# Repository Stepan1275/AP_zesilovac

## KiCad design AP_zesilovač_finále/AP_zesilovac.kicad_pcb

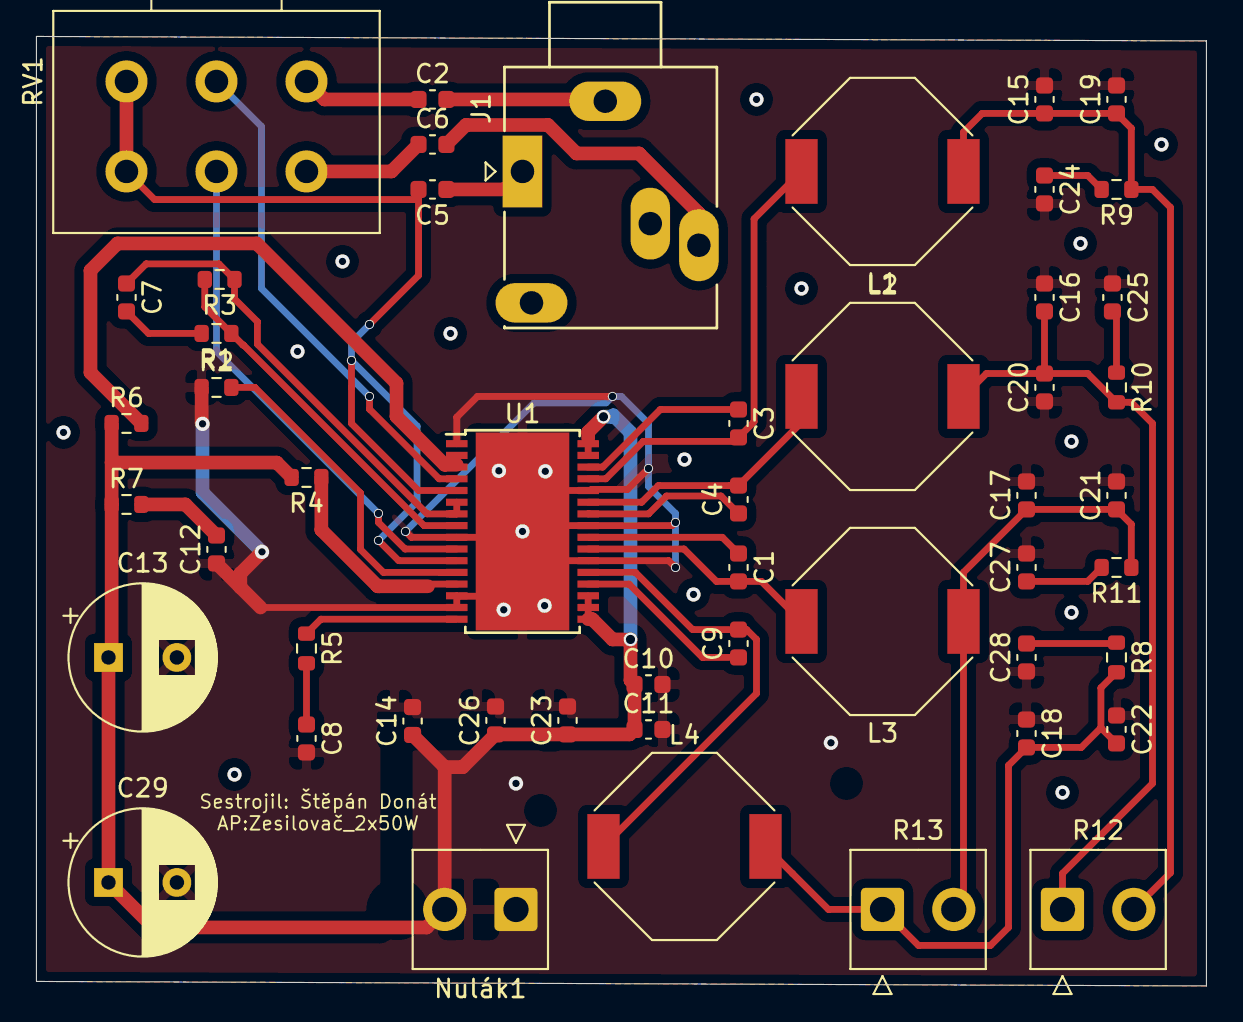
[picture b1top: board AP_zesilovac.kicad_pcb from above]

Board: 2 copper layers, 65.0 x 52.7 mm, 50 parts (0 on the bottom side), 35 nets.

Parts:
C1, C2, C3, C4, C5, C6, C7, C9: 1μF; C_0603_1608Metric
C8: 47pF; C_0603_1608Metric
C10, C19, C20, C21, C22, C23: 1nF; C_0603_1608Metric
C11, C12, C26: 100nF; C_0603_1608Metric
C13, C29: 220uF; CP_Radial_D8.0mm_P3.80mm
C14, C24, C25, C27, C28: 10nF; C_0603_1608Metric
C15, C16, C17, C18: 680nF; C_0603_1608Metric
J1: AudioJack3; Jack_3.5mm_Ledino_KB3SPRS_Horizontal
L1, L2, L3, L4: 10.0μH; L_Bourns-SRU1028_10.0x10.0mm
Nulák1: Napětí; TE_826576-2_1x02_P3.96mm_Vertical
R1: 20k; R_0603_1608Metric
R2, R3, R4, R6: 100k; R_0603_1608Metric
R5: 4,7k; R_0603_1608Metric
R7, R8, R9, R10, R11: 3.3; R_0603_1608Metric
R12, R13: L; TE_826576-2_1x02_P3.96mm_Vertical
RV1: 50k; Potentiometer_Alps_RK163_Dual_Horizontal
U1: TPA3116D2DADR-TPA3116D2DADR; HTSSOP-32-1EP_6.1x11mm_P0.65mm_EP5.2x11mm_Mask4.11x4.36mm

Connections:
4: RV1.2, U1.4
10: RV1.5, U1.10
13: R4.1, U1.13
BSNL: C9.1, U1.20
BSNR: C4.1, U1.26
BSPL: C1.1, U1.24
BSPR: C3.1, U1.30
FAULTZ: R6.2, U1.2, U1.3
GAIN_SLV: R1.1, R3.2, U1.8
GND: C8.2, C10.2, C11.2, C12.1, C13.2, C14.2, C15.2, C16.1, C17.2, C18.1, C19.2, C20.1, C21.2, C22.1, C23.2, C24.2, C25.1, C26.2, C27.2, C28.1, C29.2, Nulák1.1, R2.1, U1.1, U1.9, U1.14, U1.15, U1.22, U1.25, U1.28, U1.33
GND1: C5.2, RV1.3, RV1.6, U1.5, U1.11
GND2: C7.2, R1.2
MUTE: R2.2, U1.12
unnamed: C2.1, RV1.1
unnamed: C2.2, J1.S
unnamed: C5.1, J1.T
unnamed: C6.1, RV1.4
unnamed: C6.2, J1.R
unnamed: C8.1, R5.2
unnamed: C12.2, R7.2
unnamed: C15.1, C19.1, L1.1, R9.1, R12.2
unnamed: C16.2, C20.2, L2.2, R10.2, R12.1
unnamed: C17.1, C21.1, L3.1, R11.1, R13.2
unnamed: C18.2, C22.2, L4.2, R8.2, R13.1
unnamed: C24.1, R9.2
unnamed: C25.2, R10.1
unnamed: C27.1, R11.2
unnamed: C28.2, R8.1
OUTNL: C9.2, L4.1, U1.21
OUTNR: C4.2, L2.1, U1.27
OUTPL: C1.2, L3.2, U1.23
OUTPR: C3.2, L1.2, U1.29
PLIMIT: C7.1, R3.1, U1.6, U1.7
SYNC: R5.1, U1.16
VCC: C10.1, C11.1, C13.1, C14.1, C23.1, C26.1, C29.1, Nulák1.2, R4.2, R6.1, R7.1, U1.17, U1.18, U1.19, U1.31, U1.32

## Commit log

2020-12-17 start
2020-12-17 Create HW1
2021-01-04 jack
2021-01-12 test
2021-01-27 posledni_konrtrola
